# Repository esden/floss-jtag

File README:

Free Libre Open-Source/-Hardware JTAG/UART Adapter based on FT2232H chip.

The hardware is licensed under Creative Commons Share Alike By Attribution 3.0 (CC-BY-SA 3.0)

Copyright 2009-2010 Piotr Esden-Tempski

UART connector adapter side:
----------------------------

1: 3V3
2: TXD
3: RXD
4: GND

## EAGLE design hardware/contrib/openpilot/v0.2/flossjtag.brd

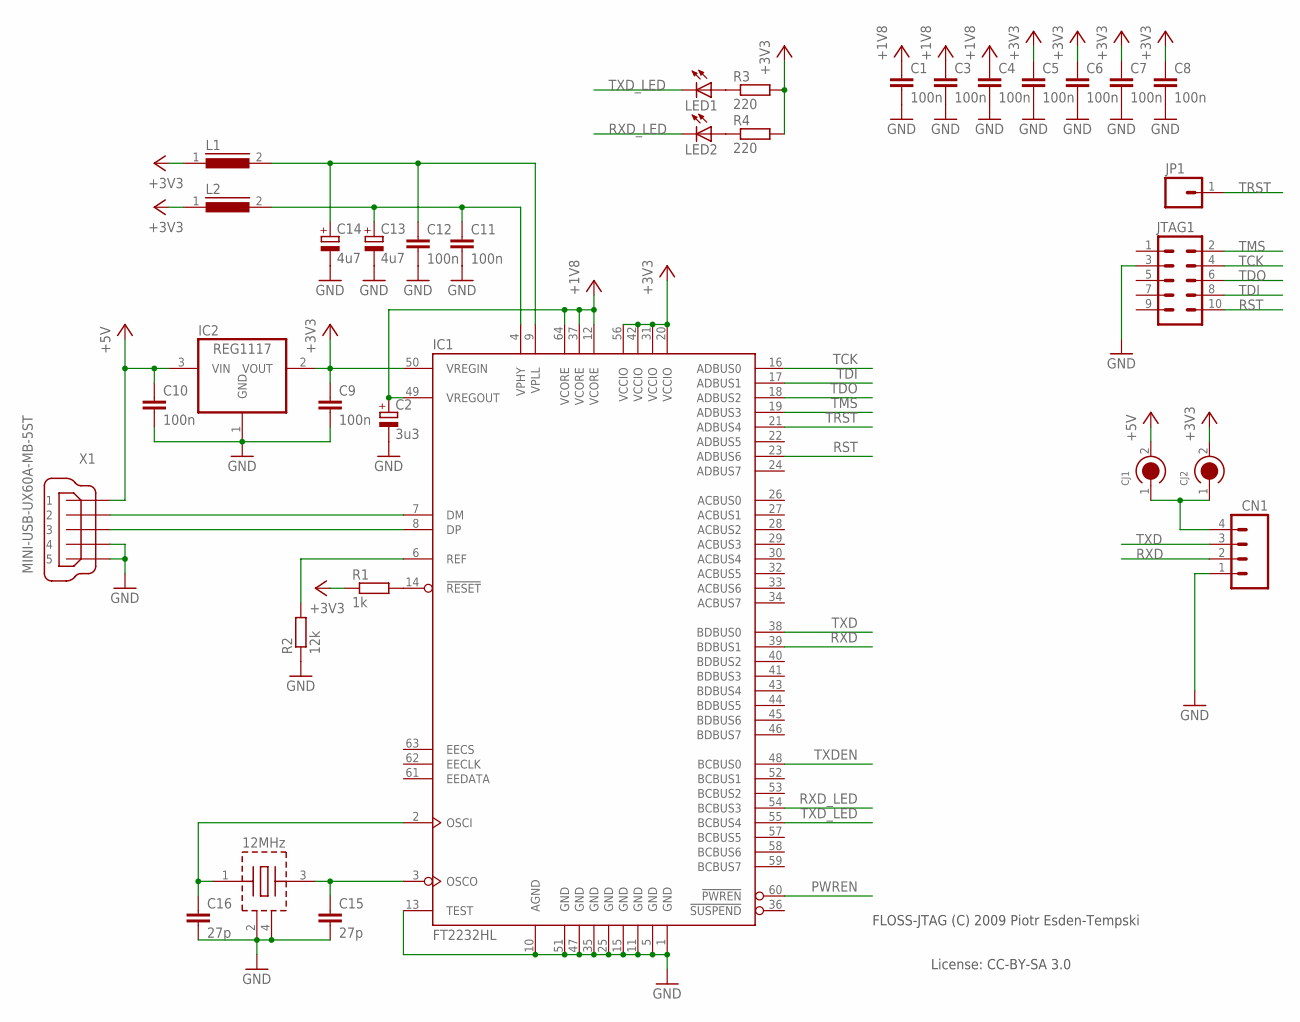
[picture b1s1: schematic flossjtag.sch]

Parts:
C1, C3, C4, C5, C6, C7, C8, C9, C10, C11, C12: 100n; C0603
C2: 3u3; A/3216-18R
C13, C14: 4u7; A/3216-18R
C15, C16: 27p; C0603
CJ1, CJ2: CIRC_JMP
CN1: SM04B-SRSS-TB
IC1: FT2232HL; LQFP64
IC2: REG1117; SOT223
JP1: PAD-0.06
JTAG1: JTAG-EDGE
L1, L2: I0603; R0603
LED1, LED2: LEDCHIP-LED0603; CHIP-LED0603
R1: 1k; R0603
R2: 12k; R0603
R3, R4: 220; R0603
X1: MINI-USB-UX60A-MB-5ST; UX60A-MB-5ST
X3: 12MHz; NX3225SA

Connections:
+3V3: C5.1, C6.1, C7.1, C8.1, C9.1, CJ2.2, IC1.20 (VCCIO), IC1.31 (VCCIO), IC1.42 (VCCIO), IC1.50 (VREGIN), IC1.56 (VCCIO), IC2.2 (VOUT), L1.1, L2.1, R1.1, R3.2, R4.2
+5V: C10.1, CJ1.2, IC2.3 (VIN), X1.1
GND: C1.2, C2.-, C3.2, C4.2, C5.2, C6.2, C7.2, C8.2, C9.2, C10.2, C11.2, C12.2, C13.-, C14.-, C15.2, C16.2, CN1.1, IC1.1 (GND), IC1.5 (GND), IC1.10 (AGND), IC1.11 (GND), IC1.13 (TEST), IC1.15 (GND), IC1.25 (GND), IC1.35 (GND), IC1.47 (GND), IC1.51 (GND), IC2.1 (GND), JTAG1.3, R2.1, X1.4, X1.5, X3.2 (GND), X3.4 (GND)
unnamed: IC1.14 (!RESET), R1.2
unnamed: IC1.6 (REF), R2.2
unnamed: IC1.7 (DM), X1.2
unnamed: IC1.8 (DP), X1.3
unnamed: CJ1.1, CJ2.1, CN1.4
unnamed: C16.1, IC1.2 (OSCI), X3.1 (XTAL)
unnamed: C12.1, C14.+, IC1.9 (VPLL), L1.2
unnamed: C11.1, C13.+, IC1.4 (VPHY), L2.2
unnamed: C15.1, IC1.3 (OSCO), X3.3 (XTAL)
unnamed: LED1.A, R3.1
unnamed: LED2.A, R4.1
PWREN: IC1.60 (!PWREN)
RST: IC1.23 (ADBUS6), JTAG1.10
RXD: CN1.2, IC1.39 (BDBUS1)
RXD_LED: IC1.54 (BCBUS3), LED2.C
TCK: IC1.16 (ADBUS0), JTAG1.4
TDI: IC1.17 (ADBUS1), JTAG1.8
TDO: IC1.18 (ADBUS2), JTAG1.6
TMS: IC1.19 (ADBUS3), JTAG1.2
TRST: IC1.21 (ADBUS4), JP1.1
TXD: CN1.3, IC1.38 (BDBUS0)
TXDEN: IC1.48 (BCBUS0)
TXD_LED: IC1.55 (BCBUS4), LED1.C
VCC: C1.1, C2.+, C3.1, C4.1, IC1.12 (VCORE), IC1.37 (VCORE), IC1.49 (VREGOUT), IC1.64 (VCORE)

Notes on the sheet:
FLOSS-JTAG (C) 2009 Piotr Esden-Tempski
License: CC-BY-SA 3.0

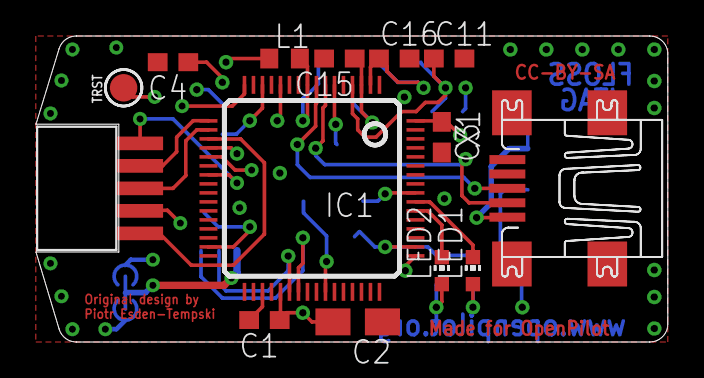
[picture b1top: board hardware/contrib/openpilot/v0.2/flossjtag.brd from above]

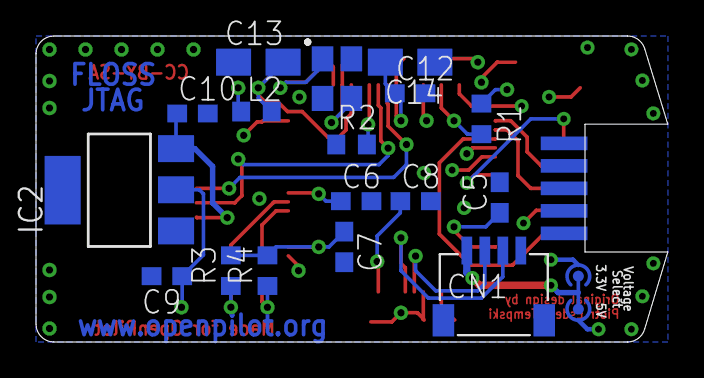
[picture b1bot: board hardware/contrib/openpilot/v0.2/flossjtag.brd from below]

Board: 4 copper layers, 35.1 x 17.0 mm, 33 parts (19 on the bottom side), 25 nets.

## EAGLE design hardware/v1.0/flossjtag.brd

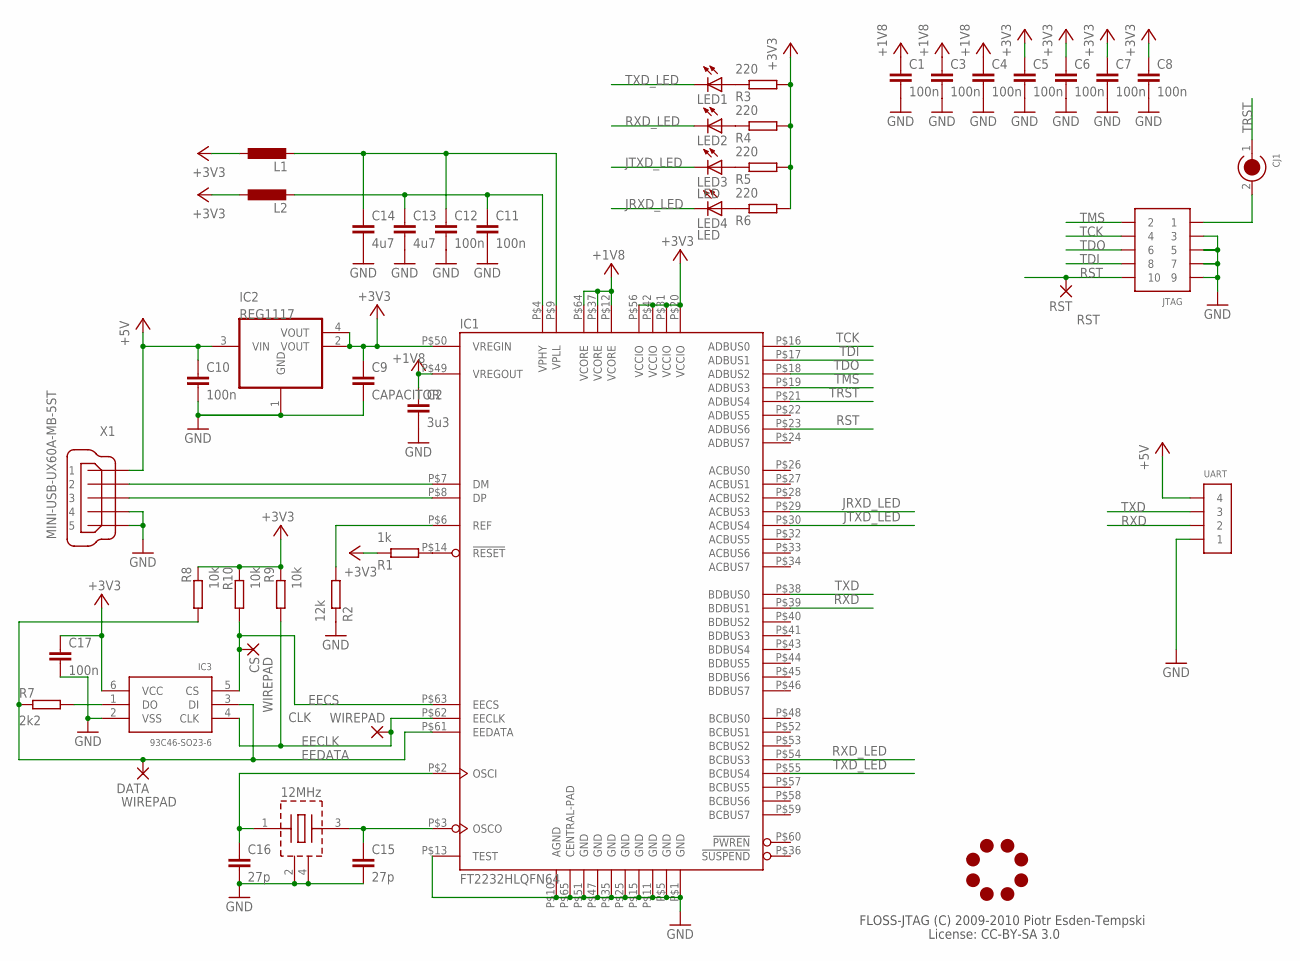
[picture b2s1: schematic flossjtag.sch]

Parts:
C1, C3, C4, C5, C6, C7, C8, C10, C11, C12, C17: 100n; 0603-CAP
C2: 3u3; 0603-CAP
C9: CAPACITOR; 0603-CAP
C13, C14: 4u7; 0603-CAP
C15, C16: 27p; 0603-CAP
CJ1: CIRC_JMP
CLK: WIREPAD; SMD1,27
CS: WIREPAD; SMD1,27
DATA: WIREPAD; SMD1,27
IC1: FT2232HLQFN64; QFN64
IC2: REG1117; SOT223
IC3: 93C46-SO23-6; SO23-6
JL1: JOBY_LOGO-6MIL; JOBY_LOGO_6MIL
JTAG: CONN_5-2-FTSH-V; FTSH-105-DV
L1, L2: INDUCTOR-0603; 0603-IND
LED1, LED2, LED3, LED4: LED; 0603-LED
R1: 1k; 0603-RES
R2: 12k; 0603-RES
R3, R4, R5, R6: 220; 0603-RES
R7: 2k2; 0603-RES
R8, R9, R10: 10k; 0603-RES
RST: RST; SMD1,27
UART: CONN_4-1; PB-53261-04
X1: MINI-USB-UX60A-MB-5ST; UX60A-MB-5ST
X3: 12MHz; NX3225SA

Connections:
+3V3: C5.P$1 (1), C6.P$1 (1), C7.P$1 (1), C8.P$1 (1), C9.P$1 (1), C17.P$1 (1), IC1.P$20 (VCCIO), IC1.P$31 (VCCIO), IC1.P$42 (VCCIO), IC1.P$50 (VREGIN), IC1.P$56 (VCCIO), IC2.2 (VOUT), IC2.4 (VOUT), IC3.6 (VCC), L1.P$1 (1), L2.P$1 (1), R1.P$1 (1), R3.P$2 (2), R4.P$2 (2), R5.P$2 (2), R6.P$2 (2), R8.P$1 (1), R9.P$1 (1), R10.P$1 (1)
+5V: C10.P$1 (1), IC2.3 (VIN), UART.4, X1.1
EECLK: CLK.1, IC1.P$62 (EECLK), IC3.4 (CLK), R9.P$2 (2)
EECS: CS.1, IC1.P$63 (EECS), IC3.5 (CS), R10.P$2 (2)
EEDATA: DATA.1, IC1.P$61 (EEDATA), IC3.3 (DI), R7.P$1 (1), R8.P$2 (2)
GND: C1.P$2 (2), C2.P$2 (2), C3.P$2 (2), C4.P$2 (2), C5.P$2 (2), C6.P$2 (2), C7.P$2 (2), C8.P$2 (2), C9.P$2 (2), C10.P$2 (2), C11.P$2 (2), C12.P$2 (2), C13.P$2 (2), C14.P$2 (2), C15.P$2 (2), C16.P$2 (2), C17.P$2 (2), IC1.P$1 (GND), IC1.P$5 (GND), IC1.P$10 (AGND), IC1.P$11 (GND), IC1.P$13 (TEST), IC1.P$15 (GND), IC1.P$25 (GND), IC1.P$35 (GND), IC1.P$47 (GND), IC1.P$51 (GND), IC1.P$65 (CENTRAL-PAD), IC2.1 (GND), IC3.2 (VSS), JTAG.3, JTAG.5, JTAG.7, JTAG.9, R2.P$1 (1), UART.1, X1.4, X1.5, X3.2 (GND), X3.4 (GND)
JRXD_LED: IC1.P$29 (ACBUS3), LED4.C
JTXD_LED: IC1.P$30 (ACBUS4), LED3.C
unnamed: IC1.P$14 (!RESET), R1.P$2 (2)
unnamed: IC1.P$6 (REF), R2.P$2 (2)
unnamed: IC1.P$7 (DM), X1.2
unnamed: IC1.P$8 (DP), X1.3
unnamed: C16.P$1 (1), IC1.P$2 (OSCI), X3.1 (XTAL)
unnamed: C12.P$1 (1), C14.P$1 (1), IC1.P$9 (VPLL), L1.P$2 (2)
unnamed: C11.P$1 (1), C13.P$1 (1), IC1.P$4 (VPHY), L2.P$2 (2)
unnamed: C15.P$1 (1), IC1.P$3 (OSCO), X3.3 (XTAL)
unnamed: LED1.A, R3.P$1 (1)
unnamed: LED2.A, R4.P$1 (1)
unnamed: LED3.A, R5.P$1 (1)
unnamed: LED4.A, R6.P$1 (1)
unnamed: IC3.1 (DO), R7.P$2 (2)
unnamed: CJ1.2, JTAG.1
RST: IC1.P$23 (ADBUS6), JTAG.10, RST.1
RXD: IC1.P$39 (BDBUS1), UART.2
RXD_LED: IC1.P$54 (BCBUS3), LED2.C
TCK: IC1.P$16 (ADBUS0), JTAG.4
TDI: IC1.P$17 (ADBUS1), JTAG.8
TDO: IC1.P$18 (ADBUS2), JTAG.6
TMS: IC1.P$19 (ADBUS3), JTAG.2
TRST: CJ1.1, IC1.P$21 (ADBUS4)
TXD: IC1.P$38 (BDBUS0), UART.3
TXD_LED: IC1.P$55 (BCBUS4), LED1.C
VCC: C1.P$1 (1), C2.P$1 (1), C3.P$1 (1), C4.P$1 (1), IC1.P$12 (VCORE), IC1.P$37 (VCORE), IC1.P$49 (VREGOUT), IC1.P$64 (VCORE)

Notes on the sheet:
FLOSS-JTAG (C) 2009-2010 Piotr Esden-Tempski
License: CC-BY-SA 3.0

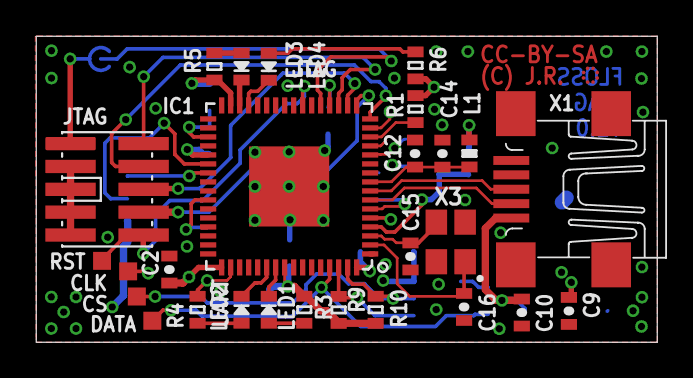
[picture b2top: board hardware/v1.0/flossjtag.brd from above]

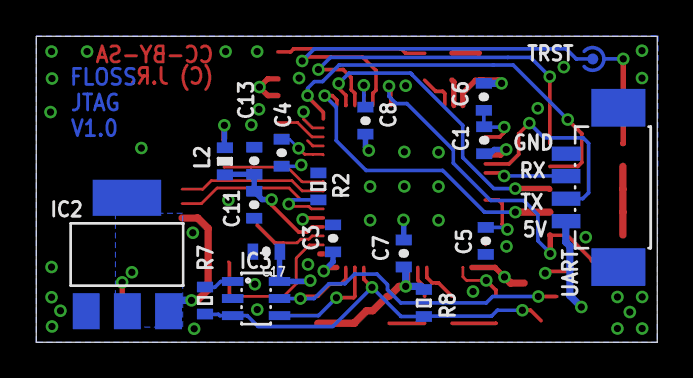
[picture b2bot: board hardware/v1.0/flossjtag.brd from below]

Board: 4 copper layers, 34.5 x 17.0 mm, 47 parts (18 on the bottom side), 33 nets.

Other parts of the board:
DRILEGEND: DRILEGEND

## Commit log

2009-10-15 Initial commit of FLOSS-JTAG.
2009-10-15 Fixed some typos.
2009-10-15 Fixed RST line, to be compatible with DLP-USB1232H, this one is already supported by OpenOCD.
2009-10-15 Connected one last airwire that I overlooked...
2009-10-15 Moved some vias so that teardrops are possible without breaking DRC.
2009-10-15 Created a teardrop version of the board.
2009-10-15 Added molex to 20pin adapter board.
2009-10-15 Added 20pin adapter teardrops version.
2009-10-15 Added makefiles for generating gerber files and panelization.
2009-10-15 Changed all vias to be closed. (Covered with soldermask)
2009-10-16 Updated CRYSTAL to have a value. Added used libraries.
2009-10-17 Made texts bigger as requested by pcbcard, added text and some vias to the adapter board.
2009-10-19 Changed distance between the boards on the panel from 3mm to 2mm. (PCBCard tabrouting is made with 2mm router)
2009-10-19 Increased text size again. Now it should be big enough!
2009-10-19 Exchanged old boring solder jumpers with new fancy ones. ^^
2009-11-12 Connected pin 5 of the usb connector to GND as it should be.
2009-11-16 Fixed footprint of the ft2232 chip.
2009-12-03 Moved the v0.1 directory to v0.2. v0.1 was broken so should not be visible anymore.
2009-12-03 Updated the version number in the board file to v0.2.
2009-12-03 Updated the teardrop version of flossjtag to the current version.
2010-01-27 Added 93C46 eeprom with sot32-6 footprint to lib.
2010-01-27 Started v0.3 with pretty-eagle-lib parts and eeprom.
2010-01-27 Added OpenPiolt (http://www.openpilot.org) derivate.
    Thanks to Angus Peart for using and adapting
    Floss-JTAG for OpenPilot.
2010-09-08 Replaced the non standard jtag connector with standard cortex.
2010-09-15 Updated silkscreen on v0.2 for easier assembly.
2010-09-15 Advances on v0.3 routing.
2010-10-18 Finished version v0.3 of flossjtag.
2010-10-20 Finished routing of fj v1.0. Some DRC errors need to be fixed though.
2010-10-20 Fixed or approved all DRC errors and warnings.
2010-10-20 Created teardropped version of fj 1.0.
2010-10-20 Added panel generation to fj 1.0
2010-10-23 Increased size of vias to 0.4mm.
2010-10-23 Added some more GND vias. Fixed some remaining DRC Errors.
2010-10-26 Added eeprom bypass capacitor.
2010-10-26 Updated teardrop version of FJ V1.0
2010-10-26 Added FJ V1.0 panel rails.
2010-10-26 Updated panel layuot definition.
2010-11-05 Added FLOSS-JTAG CrossWorks target definition file.
2011-01-01 Updated README added news about FLOSS-JTAG v1.0 availability at Joby Robotics Shop.
2015-10-06 Updated all files to the newest version of Cadsoft Eagle.
2015-10-06 Converted the readme into a markdown file. Added a note about the design file format.
2015-10-06 Improved the legend on the serial connector a bit.
2016-12-11 Copy edited.
